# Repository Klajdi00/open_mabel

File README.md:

<p align="center"><picture><source media="(prefers-color-scheme: dark)" srcset=".github/banner_dark.png"></picture></p>

# MABEL

**MABEL** is an open-source, 56-DOF mobile bimanual robot: a three-module swerve base, a
vertical lift, a pitching torso, a 3-DOF active head with stereo cameras, two 7-DOF arms
(OpenArm-derived) and two 17-DOF anthropomorphic hands (ORCA-derived). It is teleoperated
whole-body from a single Apple Vision Pro, without hand-held controllers.

This repository holds everything needed to build your own MABEL and run it. The guide
below walks through it in order: **simulate → teleoperate → collect data → train → build the
hardware → bring up the real robot.** You can stop after any step; steps 1–5 need no hardware.

Project page: <https://robotmabel.github.io/website/>

<table><tr>
<td></td>
<td></td>
<td></td>
<td></td>
</tr></table>

---

## Contents

- [Repository layout](#repository-layout)
- [Step 1 — Install](#step-1--install)
- [Step 2 — Run the robot in simulation](#step-2--run-the-robot-in-simulation)
- [Step 3 — Teleoperate with the Vision Pro](#step-3--teleoperate-with-the-vision-pro)
- [Step 4 — Collect demonstrations](#step-4--collect-demonstrations)
- [Step 5 — Curate data and train a policy](#step-5--curate-data-and-train-a-policy)
- [Step 6 — Build the hardware](#step-6--build-the-hardware)
- [Step 7 — Flash firmware and bring up the buses](#step-7--flash-firmware-and-bring-up-the-buses)
- [Step 8 — Calibrate](#step-8--calibrate)
- [Step 9 — Bring up the real robot](#step-9--bring-up-the-real-robot)
- [Step 10 — Connect over Tailscale (optional)](#step-10--connect-over-tailscale-optional)
- [Step 11 — Change the robot model](#step-11--change-the-robot-model)
- [Architecture](#architecture) · [Licensing](#licensing)

---

## Repository layout

```text
open_mabel/
├── hardware/            Bill of materials, build guide, full-robot CAD (STEP)
├── electrical/          Base carrier PCB: KiCad sources, schematic, Gerbers/drill
├── firmware/            MCU firmware + host drivers: swerve base, arms/torso/neck, lift, ORCA hands
├── hardware_bridge/     The HAL (`mabel_hw`): the only process that opens a device
├── controller/          The `mabel` control library: whole-body control, retargeting, safety gate
├── server/              Teleop gateway: one wire contract (ws :9090), video, recording
├── ros/                 ROS 2 Jazzy workspace: URDF, SLAM, Nav2, thin hardware clients
├── simulation/          Canonical MuJoCo model + 30 scenes
├── simulation_bridge/   MuJoCo HAL — the simulated twin of hardware_bridge
├── web_gui/             Browser studios: real/sim control centers, control lab, retarget lab
├── apps/                iOS and Apple Vision Pro teleoperation apps
├── sensors/             Camera bring-up (RealSense D405, ZED Mini)
├── calibration/         Actuator and arm system identification
└── robot_learning/      Imitation learning (curation → LeRobot → ACT/DP/π0) and RL (mjlab)
```

Every folder has a `README.md`; most also ship a technical report in `<folder>/docs/*.pdf`
with the equations, parameters and measured results.

---

## Step 1 — Install

Requirements: Python ≥ 3.10, Git. macOS or Ubuntu for simulation; Ubuntu 24.04 on an NVIDIA
Jetson for the real robot. A CUDA GPU is only needed for policy training and RL.

```bash
git clone <this-repo> open_mabel && cd open_mabel
conda create -n mabel python=3.11 -y && conda activate mabel

pip install -e controller/                 # the `mabel` control library
pip install -r server/requirements.txt     # gateway, cameras, MuJoCo
```

Check the install — the model should load with 67 qpos, 66 qvel, 59 actuators:

```bash
python3 -c "import mujoco; m = mujoco.MjModel.from_xml_path('simulation/mabel_mujoco/models/mabel_full.xml'); print(m.nq, m.nv, m.nu)"
python3 -m pytest controller/tests -q
```

The launch scripts look for an Anaconda interpreter in your home directory; set
`MABEL_PY=$(which python3)` to use the active environment instead.

---

## Step 2 — Run the robot in simulation

```bash
bash server/run.sh
```

This starts the MuJoCo twin (`simulation_bridge/`), the rendered robot cameras, the teleop
gateway on `:9090`, and the **Simulation Control Center** web studio. Open
<http://localhost:8097> to see the robot in 3-D, drive it with keyboard, gamepad or your
webcam, switch scenes, and send navigation goals. Press `q` in the terminal to stop
everything.

Useful variants:

```bash
bash server/run.sh -s simulation/mabel_mujoco/scenes/mabel_kitchen_fk.xml   # another scene
bash server/run.sh --test       # open field + table + graspable objects, with the MuJoCo viewer
bash server/run.sh --viewer     # also open the native MuJoCo window
bash server/run.sh --mock       # synthetic operator hands, no headset needed
```

Without the gateway, you can drive the model directly in the MuJoCo viewer:

```bash
cd simulation/mabel_mujoco
mjpython scripts/keyboard_teleop.py            # whole-body keyboard teleop
mjpython scripts/compliance.py --region whole  # push the robot around; compliant whole body
```

More: [`server/README.md`](server/README.md), [`simulation/README.md`](simulation/README.md),
[`web_gui/README.md`](web_gui/README.md).

---

## Step 3 — Teleoperate with the Vision Pro

1. Open the app in Xcode: `open apps/visionos/MabelTeleop.xcodeproj`.
2. In *Signing & Capabilities*, choose your own development team and change the bundle
   identifier from `org.example.MabelTeleop-V2` to your own namespace.
3. Build and run the **MabelTeleop** scheme on your Vision Pro.
4. Keep `bash server/run.sh` running on a computer on the same Wi-Fi. The app finds the
   gateway over Bonjour (`_mabel-teleop._tcp`); otherwise add it by IP in
   Settings → **Add robot**.
5. Enter the immersive whole-body mode: your head drives the neck and torso, your wrists the
   arms, your fingers the ORCA hands, and the drive pad the base. The stereo head camera is
   shown in front of you.

The same app drives the real robot unchanged (Step 9). Details, routes
(Wi-Fi LAN, Tailscale, Bluetooth) and tests: [`apps/visionos/README.md`](apps/visionos/README.md).
The iPhone app in [`apps/ios/`](apps/ios/README.md) speaks the same protocol and connects the same way.

---

## Step 4 — Collect demonstrations

**In simulation.** With `bash server/run.sh` running, start and stop recording from the
studio or the Vision Pro app. The gateway writes one HDF5 file per episode:

```text
dataset/simulation/vision_os/<task>/episode_XXXX.h5
```

Each frame stores every camera (JPEG RGB, uint16 depth), LiDAR, joint position/velocity/
torque, base twist, end-effector poses and the command sent to every actuator.

**On the real robot.** Run the collector next to the bring-up (Step 9); the app's record
button points at it:

```bash
python3 server/real_curation_collector.py --client visionos --control-port 9095
```

Sim and real episodes share one format. More:
[`server/docs/data_collection.md`](server/docs/data_collection.md).

---

## Step 5 — Curate data and train a policy

Training runs LeRobot in its own environment (torch + CUDA). Point MABEL at it once:

```bash
export MABEL_LEROBOT_PYTHON=/path/to/lerobot-env/bin/python
cd robot_learning
```

1. **Curate** — score episode quality and export a LeRobot dataset:
   ```bash
   HDF5_USE_FILE_LOCKING=FALSE python3 curate_export.py \
       --sessions '../real/vision_os/pick_place_*' --out-name pick_place --realm real
   ```
   For interactive review and trimming, run the Data Curation studio:
   `MABEL_DATASET_ROOT=../real/vision_os python3 -m data_curation.server` → <http://127.0.0.1:8093>.
2. **Train** — ACT, Diffusion Policy (`DP`), π0 or π0.5:
   ```bash
   python3 -m training_studio.server.mabel_train list-datasets
   python3 -m training_studio.server.mabel_train train --arch ACT \
       --dataset pick_place_001_<date> --steps 20000 --batch 8 --device cuda
   ```
3. **Evaluate / resume:**
   ```bash
   python3 -m training_studio.server.mabel_train eval   --run <run_id> --episodes 3
   python3 -m training_studio.server.mabel_train resume --run <run_id> --steps 40000
   ```

The Training Studio (`python3 -m training_studio.server`, <http://localhost:8095>) does the
same with live loss curves and closed-loop deployment in MuJoCo. Full walkthrough:
[`robot_learning/PIPELINE.md`](robot_learning/PIPELINE.md).

**Reinforcement learning** (GPU): MABEL tasks on mjlab (Isaac-Lab-style API on MuJoCo-Warp),
including whole-body control (arm + hand + lift + torso):

```bash
cd robot_learning/reinforcement_learning/mjlab && uv sync
uv run play  Mjlab-Lift-Cube-Mabel --agent zero                 # sanity check
uv run train Mjlab-Lift-Cube-Mabel --env.scene.num-envs 4096    # PPO, arms only
uv run train Mjlab-Lift-Cube-Mabel-WholeBody --env.scene.num-envs 4096   # whole-body PPO
```

---

## Step 6 — Build the hardware

1. **Order parts.** [`hardware/bom/MABEL_Build_Guide.pdf`](hardware/bom/MABEL_Build_Guide.pdf)
   lists every part with vendor links and three build tiers; the costed BOM is
   [`hardware/bom/mabel_bom.pdf`](hardware/bom/mabel_bom.pdf) (source of truth:
   `hardware/bom/data/core.csv`).
2. **Build the upstream sub-assemblies.** Arms from
   [OpenArm](https://github.com/enactic/openarm_hardware), hands from the
   [ORCA Hand](https://github.com/orcahand/orcahand_hardware), three REV MAXSwerve modules,
   and the lift column — see [`hardware/README.md`](hardware/README.md).
3. **Make the MABEL parts.** Unzip `hardware/cad/MABEL_full_assembly.step.zip` and print or
   machine the custom parts from the full-robot STEP assembly.
4. **Fabricate the base carrier board.** Zip `electrical/Motherboard/fab/` and order it from
   any 2-layer PCB service; parts are in `electrical/exports/Motherboard_schematic.pdf`.
   See [`electrical/README.md`](electrical/README.md).

---

## Step 7 — Flash firmware and bring up the buses

```bash
# Swerve base and arms/torso/neck — Teensy 4.1, PlatformIO
cd firmware/swerve_drive && pio run -e teensy41 -t upload && cd -
cd firmware/openarm_dual && pio run -t upload && cd -     # copy config/robot.json to its SD card

# Lift — Raspberry Pi Pico, MicroPython
pip install mpremote && firmware/lift/tools/deploy.sh

# ORCA hands — no flashing; check the 17 servo IDs per hand
python3 firmware/orca_hand/feetech/scripts/scan.py

# CAN (SocketCAN) — bring up and ping the DaMiao motors
firmware/can_up.sh --ping
```

Before first use, verify each DaMiao motor's `(p_max, v_max, t_max)` in the vendor tool — a
mismatch silently rescales every value on the wire. More: [`firmware/README.md`](firmware/README.md).

---

## Step 8 — Calibrate

```bash
pip install -r calibration/requirements.txt
calibration/motor_calibration/hardware/scan.sh                     # list motors (does not energise)
calibration/motor_calibration/hardware/run_hardware.sh DM-J4310 2  # friction/inertia ID of one motor
cd hardware_bridge && python3 -m mabel_hw.drivers.orcahand.calibrate --model left   # hand end-stop sweep
```

Encoder windows, joint directions and gravity feed-forward live in
[`hardware_bridge/calibration_data/mabel.json`](hardware_bridge/calibration_data/); every
driver reads them from there. Procedures: [`calibration/README.md`](calibration/README.md).

---

## Step 9 — Bring up the real robot

On the robot computer, build the ROS 2 workspace once:

```bash
cd ros && ./dev_up.sh        # conda env (RoboStack ROS 2 Jazzy) + colcon build
```

Then, from the repository root:

```bash
bash server/real_run.sh      # HAL + ROS clients + cameras + SLAM + Nav2 + gateway + Control Center
```

Open the Control Center at `http://<robot-ip>:8094`, or connect the Vision Pro app.
Subsystems without hardware stay idle; `--no-arms`, `--no-base`, `--only-hands`, etc. bring
up a subset (`bash server/real_run.sh -h`).

**Safety.** Arms come up limp; torque is enabled explicitly by the operator. Every base
twist passes the tip-over gate, which limits speed by lift height. Know where your e-stop is
before enabling torque. Read [`hardware_bridge/README.md`](hardware_bridge/README.md) (safety
section) and [`controller/README.md`](controller/README.md) first.

---

## Step 10 — Connect over Tailscale (optional)

On the same Wi-Fi the apps and browser connect directly (Bonjour discovery or the host's LAN
IP). To reach the robot from another network, install [Tailscale](https://tailscale.com) on
the robot host and on each client device, sign them into the same tailnet, and use the robot
host's `100.x.y.z` address wherever you would use its LAN IP. The protocol and ports are
identical; nothing is exposed to the public internet. To require an access code, start the
server with `MABEL_TOKEN=<your-code>` and enter the same code in the client. Details:
[`server/README.md`](server/README.md).

---

## Step 11 — Change the robot model

`simulation/mabel_mujoco/models/mabel_full.xml` is the single source of truth. After editing
it, regenerate the derived artifacts in order:

```bash
python3 ros/src/mabel_description/scripts/mjcf_to_urdf.py \
  --mjcf simulation/mabel_mujoco/models/mabel_full.xml \
  --out  ros/src/mabel_description/urdf/mabel_full.urdf \
  --mesh-prefix package://mabel_description/meshes                      # 1. MJCF → URDF
python3 ros/src/mabel_description/urdf_to_glb.py                         # 2. URDF → web rig (web_gui/shared_assets/)
python3 simulation/tools/glb_to_rig.py                                   # 3. web rig → iOS + Vision Pro rigs
python3 controller/experiments/exp_front_workspace.py --phase W3 --build # 4. arm posture table
python3 controller/experiments/wbc_stability.py                          # 5. check tip-over CoM constants
```

If step 5 reports more than ~1 cm of centre-of-mass error, update the constants in
`controller/mabel/motion_model/tip_over.py`.

---

## Architecture

Three rules hold for every data path:

1. **`hardware_bridge/` is the sole hardware owner.** Nothing else — ROS included — opens a
   bus, serial port or camera.
2. **`controller/` is the sole gate on motion.** Every command source (Vision Pro, browser,
   keyboard, gamepad, Nav2, a learned policy) is a client of one wire contract
   (`server/wire_protocol.py`); every base twist passes `safe_base_step(...)`.
3. **The MJCF is the single source of truth** for geometry, inertia and limits.

```text
command : device ─▶ server (ws :9090) ─▶ controller ─▶ hardware_bridge ─▶ robot
state   : robot  ─▶ hardware_bridge ─▶ server ─▶ devices
video   : robot  ─▶ hardware_bridge ─▶ devices            (does not pass through server)
ros     : robot  ─▶ hardware_bridge ─▶ ROS 2 ─▶ SLAM / Nav2 / rviz
```

The simulated robot speaks the same contracts, so every client and the controller run
unchanged against the twin.

## Licensing

Software: Apache-2.0 ([`LICENSE`](LICENSE)). Hardware design files: CERN-OHL-S-2.0
([`LICENSE-HARDWARE.txt`](LICENSE-HARDWARE.txt)). Documentation and media: CC BY 4.0
([`LICENSE-DOCS.txt`](LICENSE-DOCS.txt)). Upstream components:
[`THIRD_PARTY_NOTICES.md`](THIRD_PARTY_NOTICES.md).

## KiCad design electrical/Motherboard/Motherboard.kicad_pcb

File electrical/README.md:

# electrical — base carrier board

The only custom PCB: a Teensy 4.1 carrier that runs the swerve base. Everything else is
off-the-shelf (see [`../hardware/bom/`](../hardware/bom/)).

| | |
|---|---|
| Function | 3× CAN (one per swerve module), Ethernet to the robot computer, 24 V to three XT30 outputs, BNO085 IMU (SPI) |
| Board | 2 layers, 95.55 × 83.05 mm, 1.6 mm, KiCad 10 |
| Status | Fabricated and bench-validated (flash, Ethernet, all three CAN buses) |

| Top | Bottom |
|---|---|
|  |  |

## Files

```text
Motherboard/            KiCad project: schematic sheets (power, can, untitled = IMU), layout, parts/
Motherboard/fab/        Gerbers + drill — what was fabricated
exports/                schematic PDF, layout PDF, top/bottom SVG, assembled-board STEP
```

## Order and assemble

1. Zip `Motherboard/fab/` and upload it to any 2-layer PCB service (stack-up in `fab/Motherboard-job.gbrjob`).
2. Source parts from the schematic (`exports/Motherboard_schematic.pdf`) and the BOM.
3. Flash the firmware: [`../firmware/swerve_drive/`](../firmware/swerve_drive/).

`CAN_Transiever.kicad_sch` and `IMU.kicad_sch` are unused stubs.

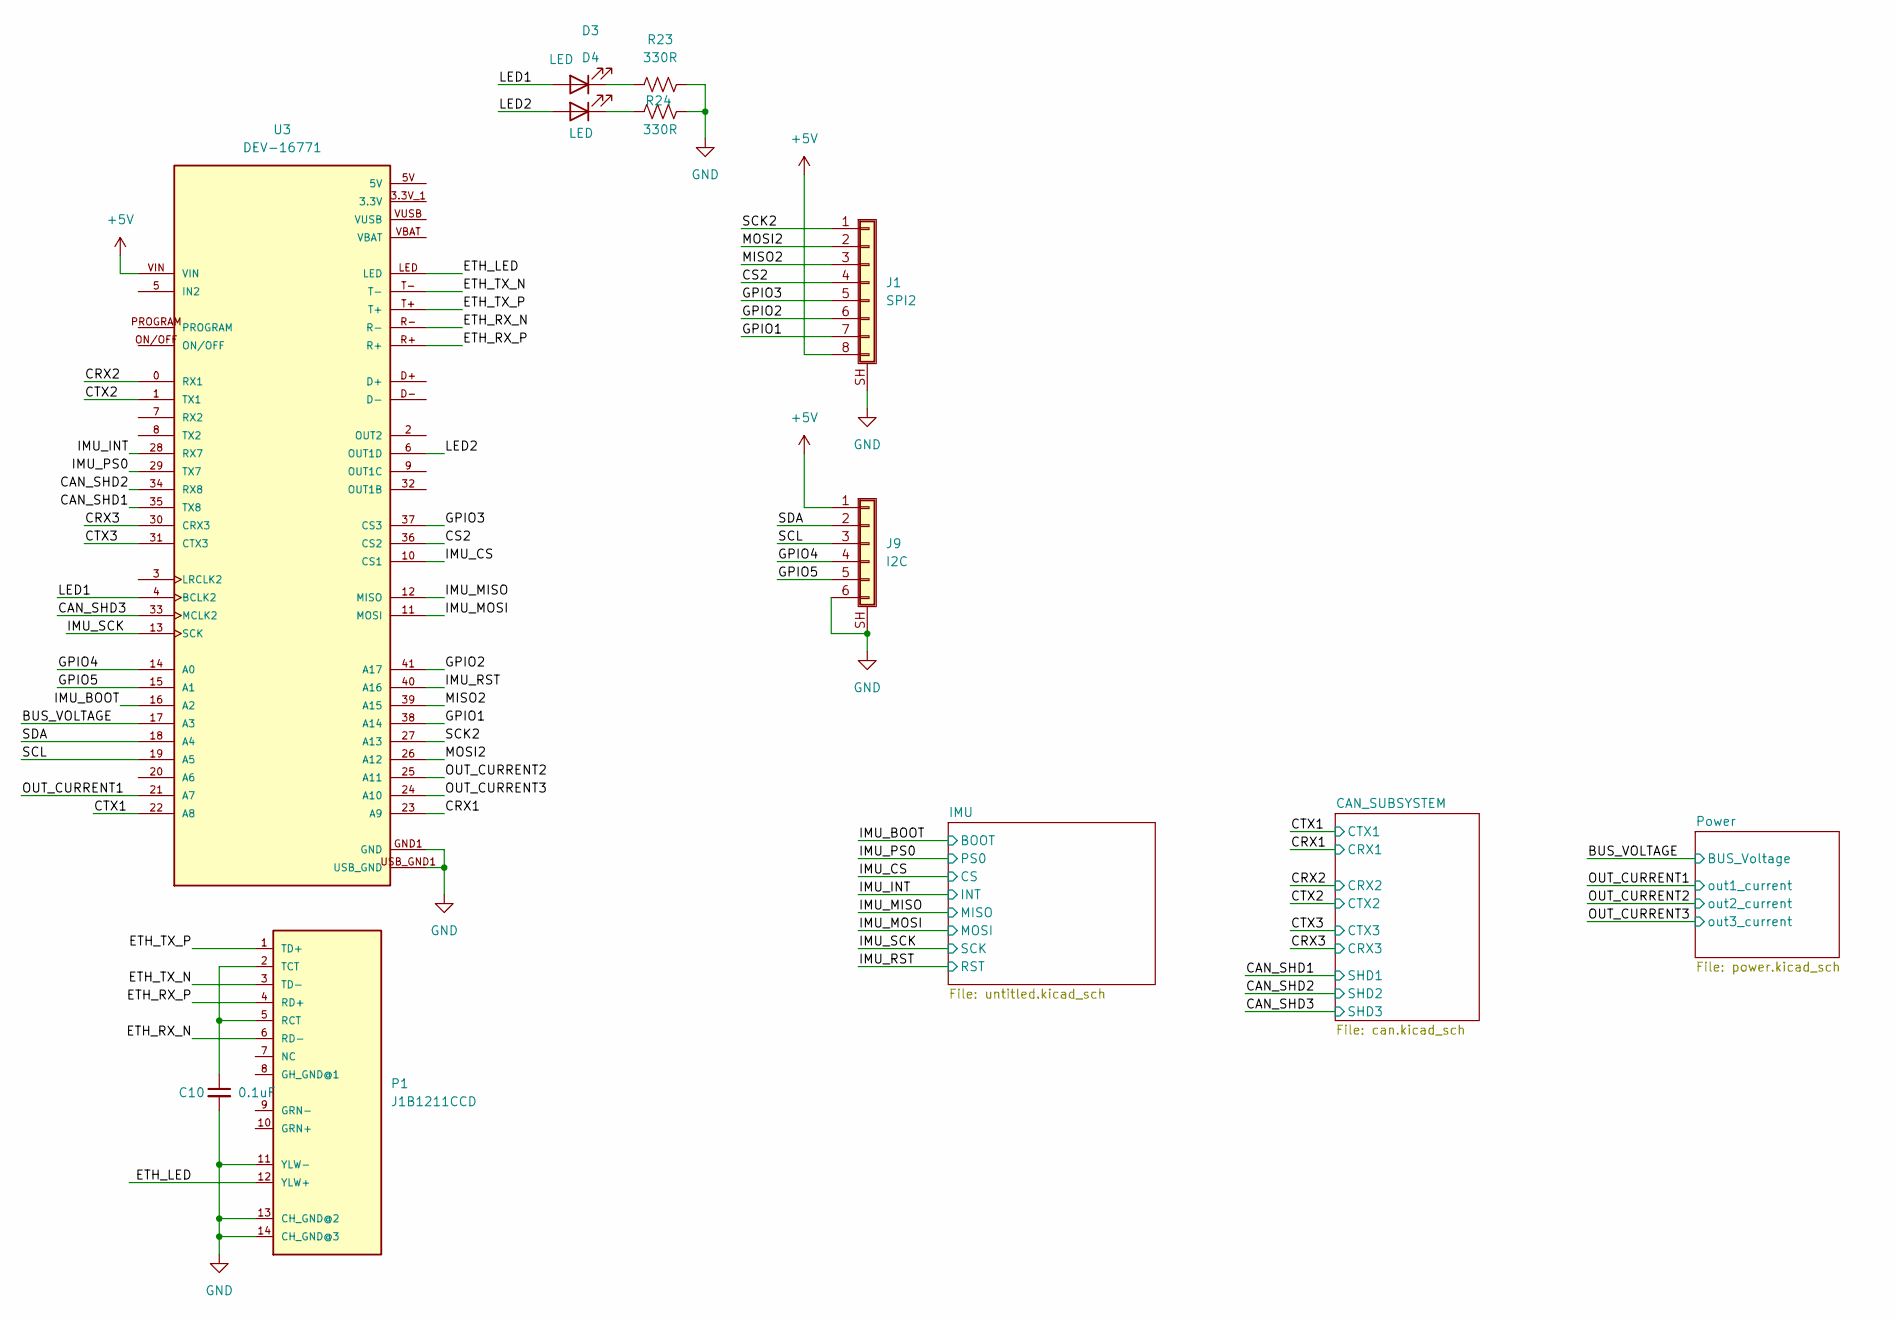
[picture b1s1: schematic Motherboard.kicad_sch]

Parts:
C10: 0.1uF; C_0805_2012Metric
D3, D4: LED; LED_0805_2012Metric
J1: SPI2; JST_SH_SM08B-SRSS-TB_1x08-1MP_P1.00mm_Horizontal
J9: I2C; JST_SH_SM06B-SRSS-TB_1x06-1MP_P1.00mm_Horizontal
P1: J1B1211CCD
R23, R24: 330R; R_0805_2012Metric
U3: DEV-16771; Teensy41; PARTREV 4.1

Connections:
3.3V: U3.3.3V_1 (3.3V), U3.3.3V_2 (3.3V), U3.3.3V_3 (3.3V)
+5V: J1.8, J9.1, U3.VIN; also elsewhere on the board
/BUS_VOLTAGE: U3.17 (A3); also elsewhere on the board
/CAN_SHD1: U3.35 (TX8); also elsewhere on the board
/CAN_SHD2: U3.34 (RX8); also elsewhere on the board
/CAN_SHD3: U3.33 (MCLK2); also elsewhere on the board
/CRX1: U3.23 (A9); also elsewhere on the board
/CRX2: U3.0 (RX1); also elsewhere on the board
/CRX3: U3.30 (CRX3); also elsewhere on the board
/CS2: J1.4, U3.36 (CS2)
/CTX1: U3.22 (A8); also elsewhere on the board
/CTX2: U3.1 (TX1); also elsewhere on the board
/CTX3: U3.31 (CTX3); also elsewhere on the board
/ETH_LED: P1.12 (YLW+), U3.LED
/ETH_RX_N: P1.6 (RD-), U3.R-
/ETH_RX_P: P1.4 (RD+), U3.R+
/ETH_TX_N: P1.3 (TD-), U3.T-
/ETH_TX_P: P1.1 (TD+), U3.T+
/GPIO1: J1.7, U3.38 (A14)
/GPIO2: J1.6, U3.41 (A17)
/GPIO3: J1.5, U3.37 (CS3)
/GPIO4: J9.4, U3.14 (A0)
/GPIO5: J9.5, U3.15 (A1)
/IMU_BOOT: U3.16 (A2); also elsewhere on the board
/IMU_CS: U3.10 (CS1); also elsewhere on the board
/IMU_INT: U3.28 (RX7); also elsewhere on the board
/IMU_MISO: U3.12 (MISO); also elsewhere on the board
/IMU_MOSI: U3.11 (MOSI); also elsewhere on the board
/IMU_PS0: U3.29 (TX7); also elsewhere on the board
/IMU_RST: U3.40 (A16); also elsewhere on the board
/IMU_SCK: U3.13 (SCK); also elsewhere on the board
/LED1: D3.2 (A), U3.4 (BCLK2)
/LED2: D4.2 (A), U3.6 (OUT1D)
/MISO2: J1.3, U3.39 (A15)
/MOSI2: J1.2, U3.26 (A12)
/OUT_CURRENT1: U3.21 (A7); also elsewhere on the board
/OUT_CURRENT2: U3.25 (A11); also elsewhere on the board
/OUT_CURRENT3: U3.24 (A10); also elsewhere on the board
/SCK2: J1.1, U3.27 (A13)
/SCL: J9.3, U3.19 (A5)
/SDA: J9.2, U3.18 (A4)
GND: C10.2, J1.MP, J1.SH (Shield), J9.6, J9.MP, J9.SH (Shield), P1.11 (YLW-), P1.13 (CH_GND@2), P1.14 (CH_GND@3), R23.2, R24.2, U3.GND1 (GND), U3.GND2 (GND), U3.GND3 (GND), U3.GND4 (GND), U3.GND5 (GND), U3.USB_GND1 (USB_GND), U3.USB_GND2 (USB_GND); also elsewhere on the board
unnamed: D3.1 (K), R23.1
unnamed: D4.1 (K), R24.1
unnamed: C10.1, P1.2 (TCT), P1.5 (RCT)

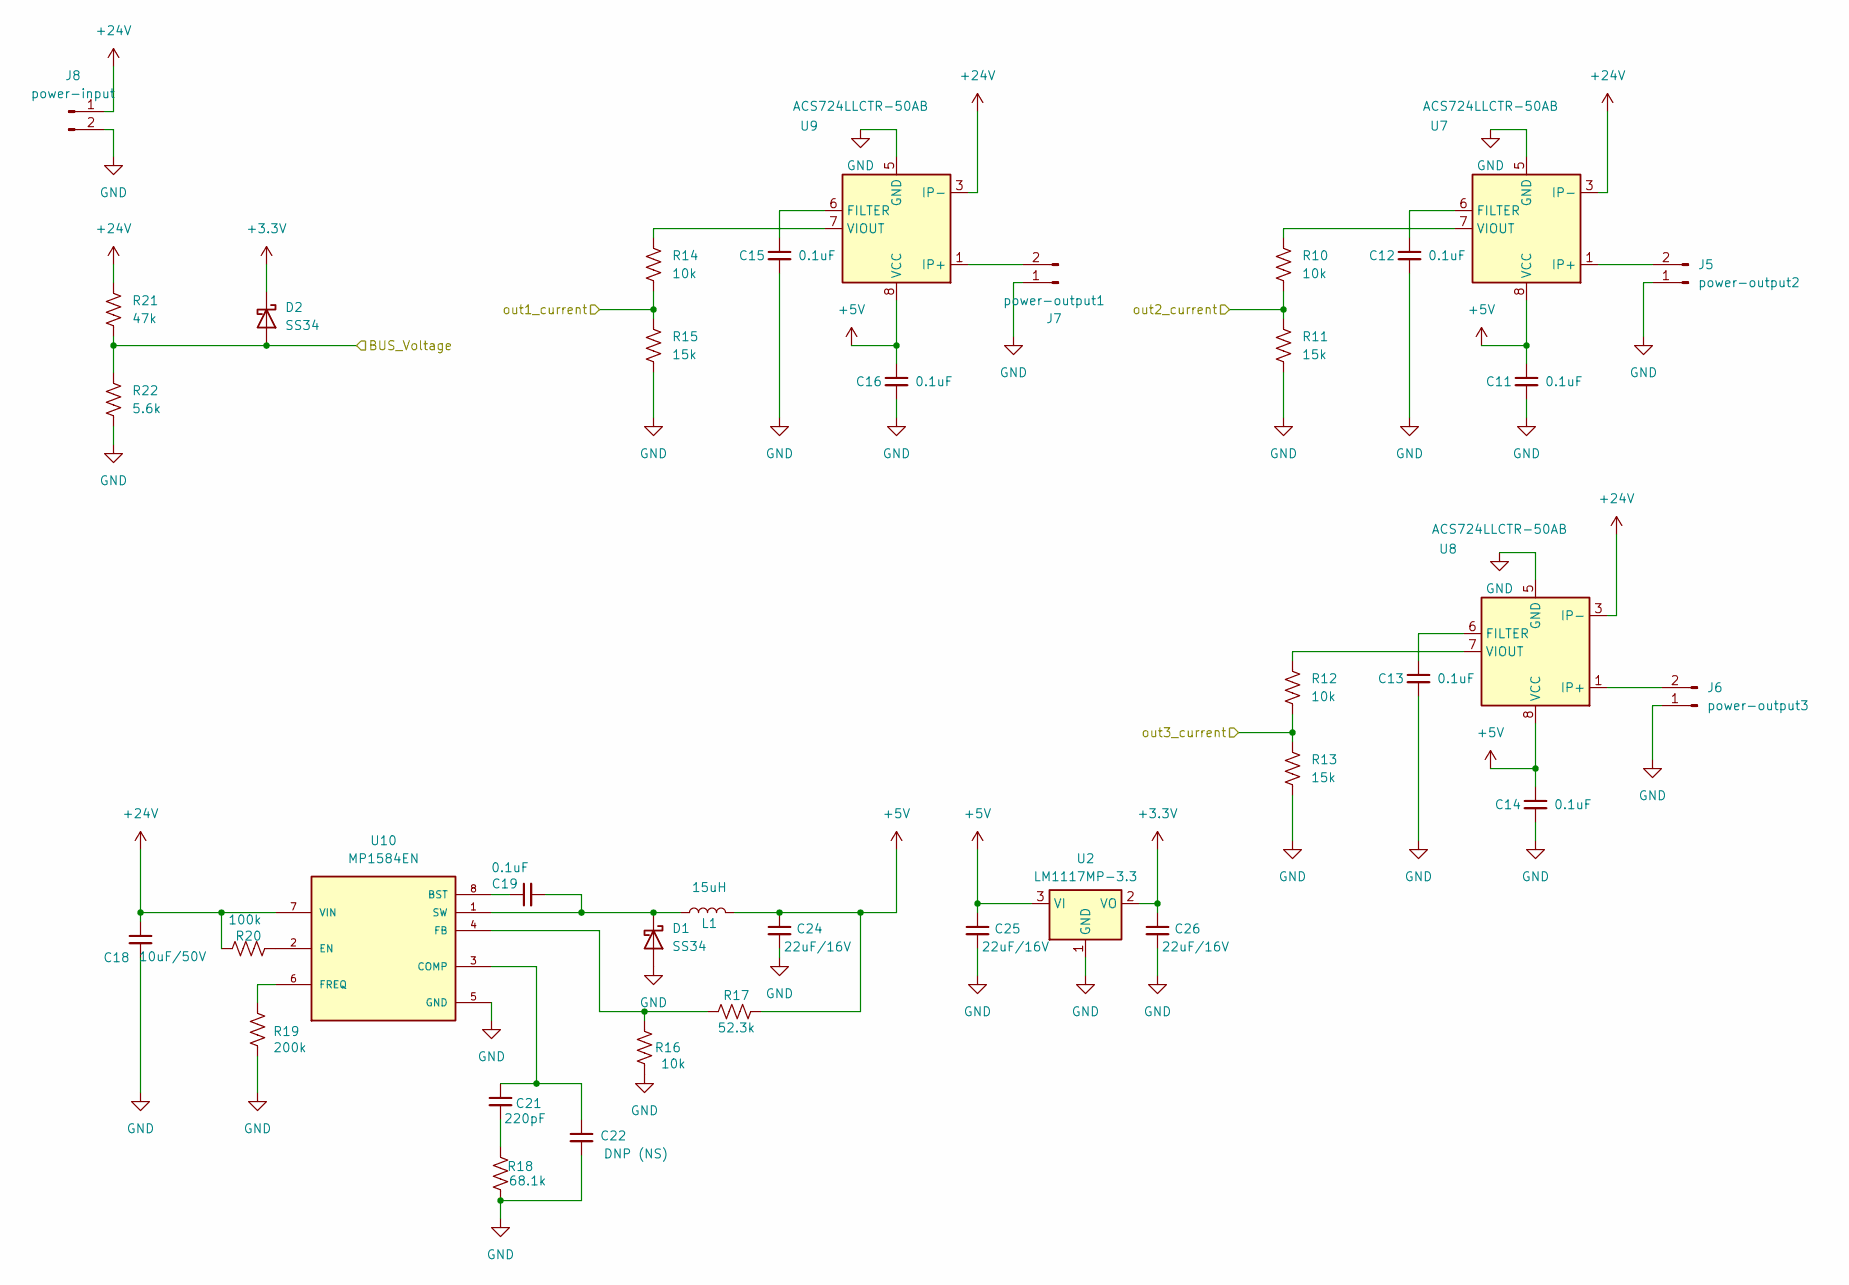
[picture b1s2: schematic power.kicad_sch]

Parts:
C11, C12, C13, C14, C15, C16, C19: 0.1uF; C_0805_2012Metric
C18: 10uF/50V; C_1210_3225Metric
C21: 220pF; C_0805_2012Metric
C22: DNP (NS); C_0805_2012Metric
C24, C25, C26: 22uF/16V; C_1206_3216Metric
D1, D2: SS34; D_SMA
J5: power-output2; AMASS_XT30PW-M_1x02_P2.50mm_Horizontal
J6: power-output3; AMASS_XT30PW-M_1x02_P2.50mm_Horizontal
J7: power-output1; AMASS_XT30PW-M_1x02_P2.50mm_Horizontal
J8: power-input; AMASS_XT60-F_1x02_P7.20mm_Vertical
L1: 15uH; L_APV_APH0630
R10, R12, R14, R16: 10k; R_0805_2012Metric
R11, R13, R15: 15k; R_0805_2012Metric
R17: 52.3k; R_0805_2012Metric
R18: 68.1k; R_0805_2012Metric
R19: 200k; R_0805_2012Metric
R20: 100k; R_0805_2012Metric
R21: 47k; R_0805_2012Metric
R22: 5.6k; R_0805_2012Metric
U2: LM1117MP-3.3; SOT-223-3_TabPin2
U7, U8, U9: ACS724LLCTR-50AB; SOIC-8_3.9x4.9mm_P1.27mm
U10: MP1584EN; SOIC127P600X170-9N

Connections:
+3.3V: C26.1, D2.1 (K), U2.2 (VO); also elsewhere on the board
+5V: C11.1, C14.1, C16.1, C24.1, C25.1, L1.2, R17.2, U2.3 (VI), U7.8 (VCC), U8.8 (VCC), U9.8 (VCC); also elsewhere on the board
+24V: C18.1, J8.1, R20.1, R21.1, U7.3 (IP-), U7.4 (IP-), U8.3 (IP-), U8.4 (IP-), U9.3 (IP-), U9.4 (IP-), U10.7 (VIN)
/BUS_VOLTAGE: D2.2 (A), R21.2, R22.1; also elsewhere on the board
/OUT_CURRENT1: R14.2, R15.1; also elsewhere on the board
/OUT_CURRENT2: R10.2, R11.1; also elsewhere on the board
/OUT_CURRENT3: R12.2, R13.1; also elsewhere on the board
GND: C11.2, C12.2, C13.2, C14.2, C15.2, C16.2, C18.2, C22.2, C24.2, C25.2, C26.2, D1.2 (A), J5.1, J6.1, J7.1, J8.2, R11.2, R13.2, R15.2, R16.2, R18.2, R19.2, R22.2, U2.1 (GND), U7.5 (GND), U8.5 (GND), U9.5 (GND), U10.5 (GND), U10.9 (GND); also elsewhere on the board
unnamed: C21.2, R18.1
unnamed: C19.2, D1.1 (K), L1.1, U10.1 (SW)
unnamed: J5.2, U7.1 (IP+), U7.2 (IP+)
unnamed: J6.2, U8.1 (IP+), U8.2 (IP+)
unnamed: J7.2, U9.1 (IP+), U9.2 (IP+)
unnamed: C12.1, U7.6 (FILTER)
unnamed: R10.1, U7.7 (VIOUT)
unnamed: C13.1, U8.6 (FILTER)
unnamed: R12.1, U8.7 (VIOUT)
unnamed: C15.1, U9.6 (FILTER)
unnamed: R14.1, U9.7 (VIOUT)
unnamed: C19.1, U10.8 (BST)
unnamed: C21.1, C22.1, U10.3 (COMP)
unnamed: R20.2, U10.2 (EN)
unnamed: R16.1, R17.1, U10.4 (FB)
unnamed: R19.1, U10.6 (FREQ)

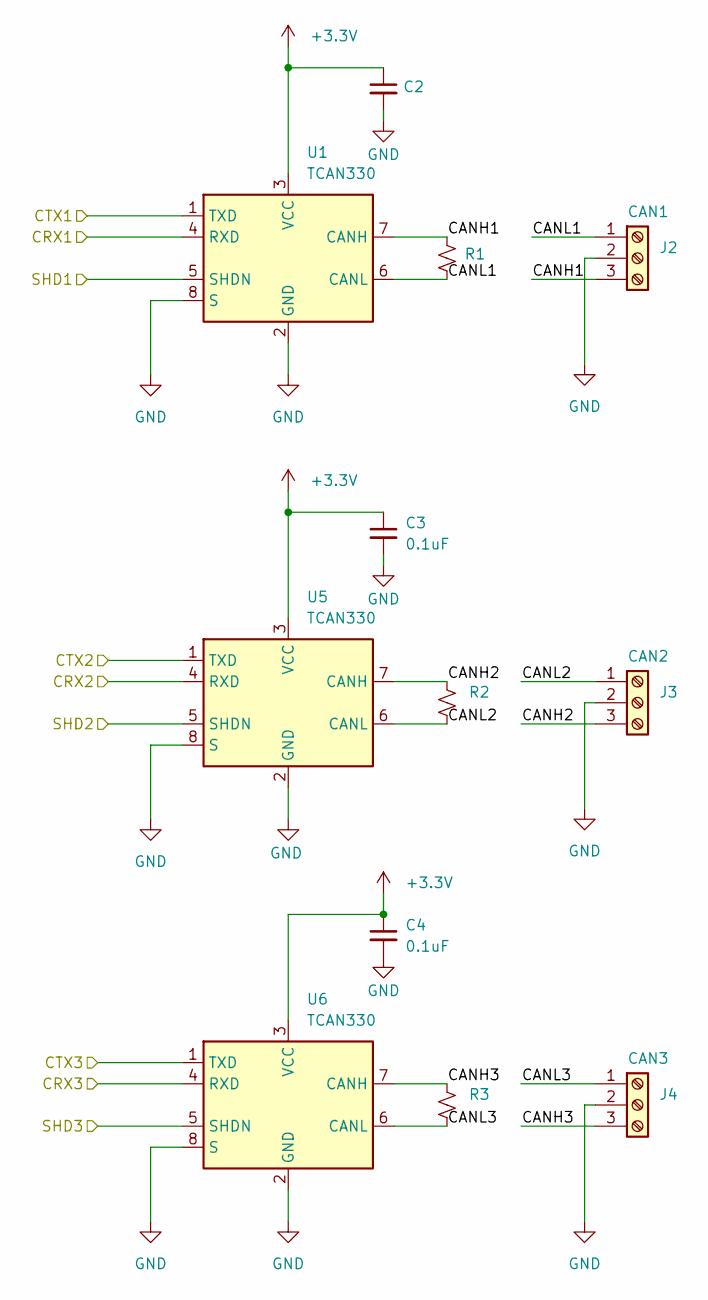
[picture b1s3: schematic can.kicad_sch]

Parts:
C2, C3, C4: 0.1uF; C_0805_2012Metric
J2: CAN1; TerminalBlock_MaiXu_MX126-5.0-03P_1x03_P5.00mm
J3: CAN2; TerminalBlock_MaiXu_MX126-5.0-03P_1x03_P5.00mm
J4: CAN3; TerminalBlock_MaiXu_MX126-5.0-03P_1x03_P5.00mm
R1, R2, R3: 120R; R_0805_2012Metric_Pad1.20x1.40mm_HandSolder
U1, U5, U6: TCAN330; TSOT-23-8

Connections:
+3.3V: C2.1, C3.1, C4.1, U1.3 (VCC), U5.3 (VCC), U6.3 (VCC); also elsewhere on the board
/CAN_SHD1: U1.5 (SHDN); also elsewhere on the board
/CAN_SHD2: U5.5 (SHDN); also elsewhere on the board
/CAN_SHD3: U6.5 (SHDN); also elsewhere on the board
/CAN_SUBSYSTEM/CANH1: J2.3, R1.1, U1.7 (CANH)
/CAN_SUBSYSTEM/CANH2: J3.3, R2.1, U5.7 (CANH)
/CAN_SUBSYSTEM/CANH3: J4.3, R3.1, U6.7 (CANH)
/CAN_SUBSYSTEM/CANL1: J2.1, R1.2, U1.6 (CANL)
/CAN_SUBSYSTEM/CANL2: J3.1, R2.2, U5.6 (CANL)
/CAN_SUBSYSTEM/CANL3: J4.1, R3.2, U6.6 (CANL)
/CRX1: U1.4 (RXD); also elsewhere on the board
/CRX2: U5.4 (RXD); also elsewhere on the board
/CRX3: U6.4 (RXD); also elsewhere on the board
/CTX1: U1.1 (TXD); also elsewhere on the board
/CTX2: U5.1 (TXD); also elsewhere on the board
/CTX3: U6.1 (TXD); also elsewhere on the board
GND: C2.2, C3.2, C4.2, J2.2, J3.2, J4.2, U1.2 (GND), U1.8 (S), U5.2 (GND), U5.8 (S), U6.2 (GND), U6.8 (S); also elsewhere on the board

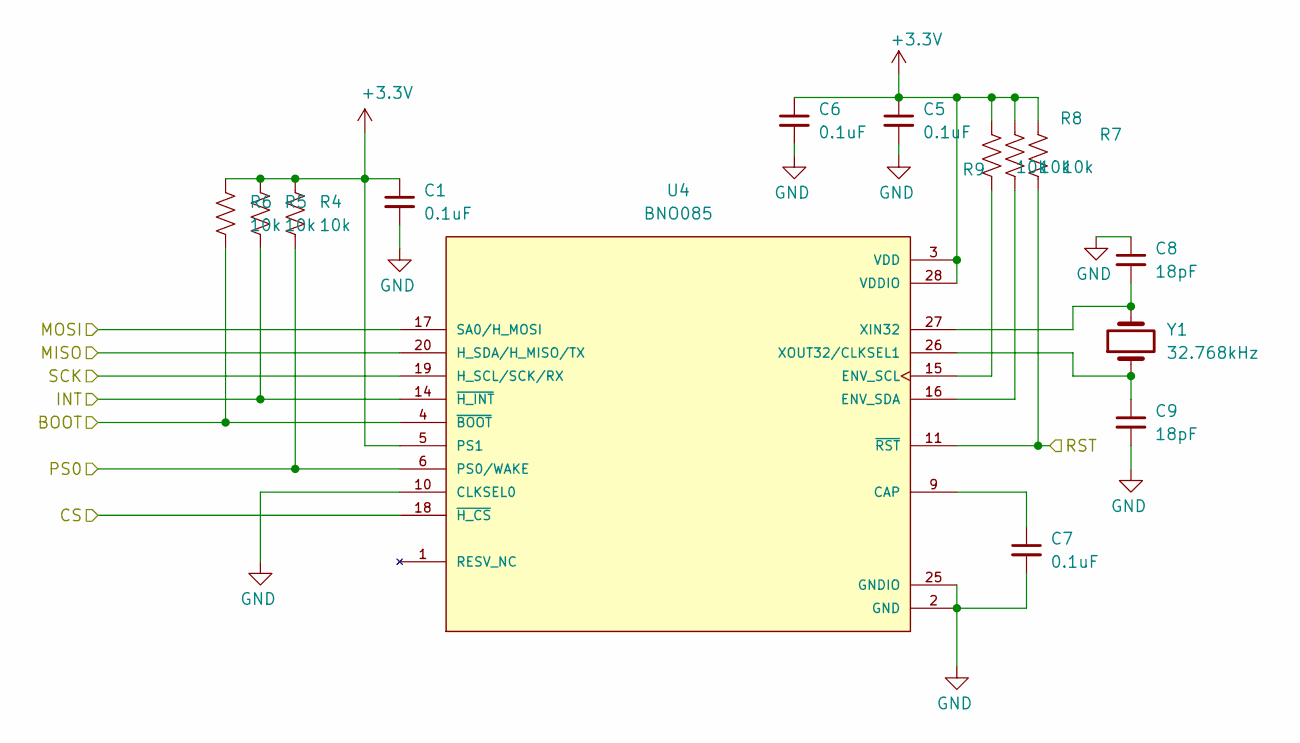
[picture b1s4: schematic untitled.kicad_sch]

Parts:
C1, C5, C6, C7: 0.1uF; C_0805_2012Metric
C8, C9: 18pF; C_0805_2012Metric
R4, R5, R6, R7, R8, R9: 10k; R_0805_2012Metric
U4: BNO085; IC_BNO085; PARTREV v1.17
Y1: 32.768kHz; Crystal_SMD_3215-2Pin_3.2x1.5mm

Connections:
+3.3V: C1.1, C5.1, C6.1, R4.1, R5.1, R6.1, R7.1, R8.1, R9.1, U4.3 (VDD), U4.5 (PS1), U4.28 (VDDIO); also elsewhere on the board
/IMU_BOOT: R6.2, U4.4 (~BOOT); also elsewhere on the board
/IMU_CS: U4.18 (~H_CS); also elsewhere on the board
/IMU_INT: R5.2, U4.14 (~H_INT); also elsewhere on the board
/IMU_MISO: U4.20 (H_SDA/H_MISO/TX); also elsewhere on the board
/IMU_MOSI: U4.17 (SA0/H_MOSI); also elsewhere on the board
/IMU_PS0: R4.2, U4.6 (PS0/WAKE); also elsewhere on the board
/IMU_RST: R7.2, U4.11 (~RST); also elsewhere on the board
/IMU_SCK: U4.19 (H_SCL/SCK/RX); also elsewhere on the board
GND: C1.2, C5.2, C6.2, C7.2, C8.1, C9.2, U4.2 (GND), U4.10 (CLKSEL0), U4.25 (GNDIO); also elsewhere on the board
unnamed: C7.1, U4.9 (CAP)
unnamed: R9.2, U4.15 (ENV_SCL)
unnamed: R8.2, U4.16 (ENV_SDA)
unnamed: C8.2, U4.27 (XIN32), Y1.2
unnamed: C9.1, U4.26 (XOUT32/CLKSEL1), Y1.1

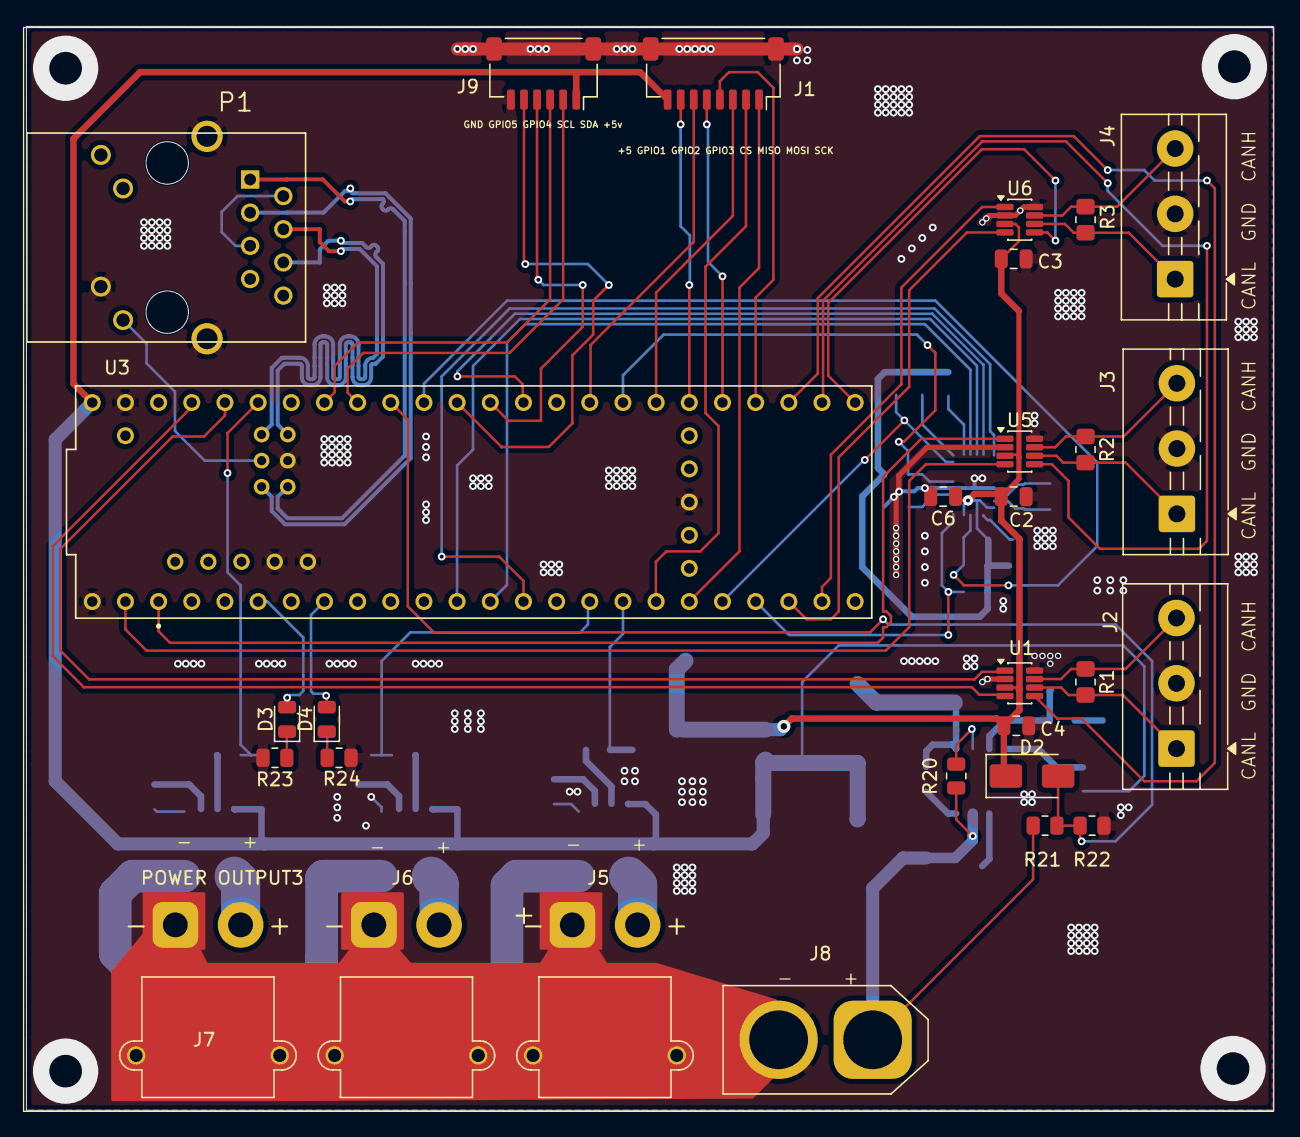
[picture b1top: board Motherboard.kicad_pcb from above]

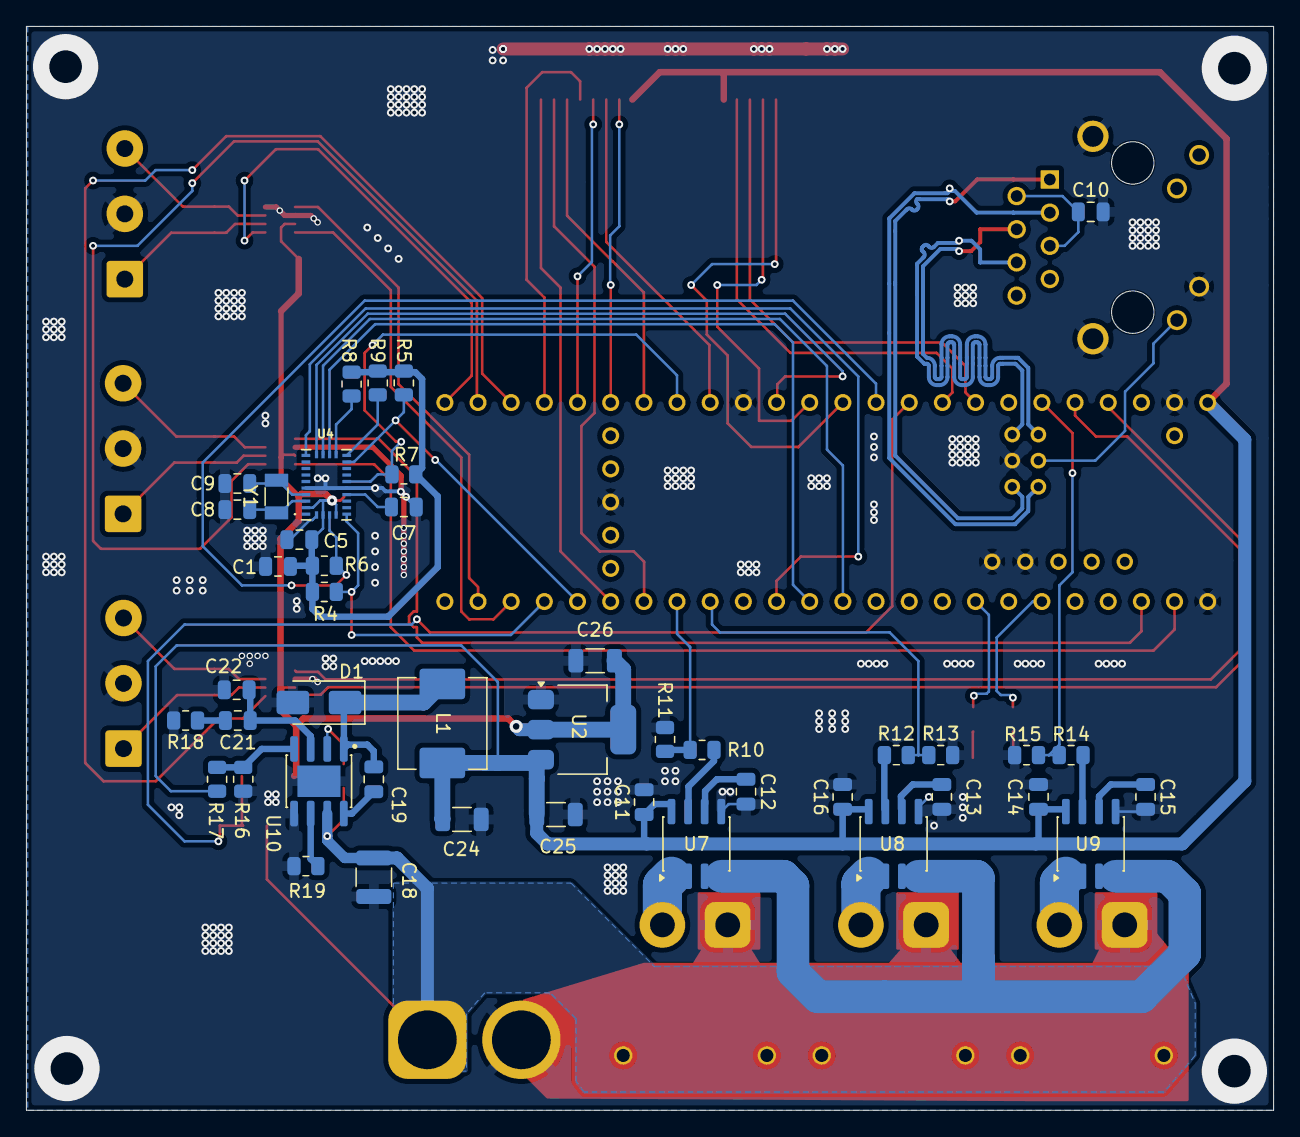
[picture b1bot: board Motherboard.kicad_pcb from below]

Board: 2 copper layers, 95.5 x 83.0 mm, 73 parts (44 on the bottom side), 74 nets.
